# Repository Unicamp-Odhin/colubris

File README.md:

# Estação metereologica LoRaWAN | Colubris

A Colubris é uma placa de hardware aberto baseada no microcontrolador ESP32-S2 e equipada com um módulo LoRa SX1262 integrado. Além disso, ela possui um sistema de gerenciamento de bateria que permite carregar e utilizar baterias diretamente pela placa. A principal finalidade da Colubris é equipar estações meteorológicas que operarão em áreas remotas, mas ela é versátil o suficiente para ser usada em outros dispositivos que necessitem de comunicação de longo alcance.

## Desenvolvedores:

Autor: Julio Nunes Avelar.

## Hardware

Principal:

- ESP32S2/ESP32
- EByte E22-900M22 (SX1262)
- TP4056
- DW01
- 8205A
- Mosfet Canal P IRF4905 ou IRF9540
- Diodo Schottky 1n5819
- PCB impressa
- Botões
- Resistores diversos
- Capacitores diveros

A lista completa pode ser consultada na [documentação](https://embarcacoes.ic.unicamp.br/colubris/build/)

Opcional:

- Modulo de Carga TP4056
- Bateria 18650 4.2V 2600mAh
- DHT22
- Sensor de Umidade do Solo
- Sensor de Nivel de Água
- Sensor de Chuva
- Sensor de Vento
- BME280
- BH1750
- Display OLED 0.96" 128x64 I2C
- Case 3D impressa em ABS

## Software

- [ESP-IDF](https://docs.espressif.com/projects/esp-idf/en/latest/esp32/)

## Pré-requisitos:

- [ESP-IDF](https://docs.espressif.com/projects/esp-idf/en/latest/esp32/get-started/).

Você precisara do ESPIDF para compilar e gravar o Firmware na Placa.

## Configurações:

O Firmware está localizado em colubris, para acessar o diretorio use:

```bash
cd colubris
```

## Menu config:

Para gravar o firmware será necessario realizar alguns ajustes no menu config.

Para "invocar" o ESPID, utilize:

```bash
get_idf
```

Após invocar o IDF, nó diretorio, será necessario escolher o MCU, para utilizar o ESP32S2, utilize:

```bash
idf.py set-target esp32s2
```

Se você estiver usando a extensão do VS-Code, existe uma opção para isso no menu inferior (Elá tem uma caixa com engrenagens como icone e do lado esta escrito esp32 ou esp32s2).

Após escolher o MCU, sera necessario realizar algumas configurações no menu config.

Para acessar o menuconfig utilize:

```bash
idf.py menuconfig
```

ou utilize a opção da extensão do VS-Code (Esta opção também está no menu inferior e tem como icone uma unica engrenagem),

Após acessar menuconfig, configure as seguintes opções:

- Configure a flash com 80mhz.
- Coloque a flash com tamanho minimo de 4 MBs.
- Escolha uma tabela de partições personalizadas.
- Coloque a frequencia da CPU em 240mhz.
- Habilite o https_client.
- Habilite a calibração do ADC.
- Habilite o componente esp_https_server.

Após realizar essas configurações, salve e saia.

## Gravando:

Para realizar a gravação primeiro será necessario realizar a compilação do firmware, é possivel compilar utilizando o comando

```bash
idf.py build
```

Após compilar o firmware para gravalo utilize:

```bash
idf.py flash
```

Caso queira utilizar o monitor serial para ver os logs, utilize:

```bash
idf.py monitor
```

Para executar tudo de uma vez, utilize:

```bash
idf.py build flash monitor
```

Esse passo a passo também pode ser realizado pela extensão do ESPIDF para o VS-Code, basta selecionar a opção: **"ESP-IDF build, flash and monitor"**.

## Organização do Projeto

O projeto é organizado em sete pastas principais:

- **3d-design**: Esta pasta contém os modelos 3D desenvolvidos para o projeto.

- **docs**: Toda a documentação dos componentes e do projeto está localizada nesta pasta.

- **colubris**: Esta pasta armazena o firmware oficial do projeto.

- **documents**: Nesta pasta, você encontrará esquemáticos compilados e datasheets relacionados ao projeto.

- **kicad-project**: Aqui estão o projeto KiCad da placa de circuito impresso (PCB) e os esquemáticos do projeto.

- **examples**: Esta pasta oferece exemplos de uso do projeto para facilitar a implementação.

O projeto foi organizado dessa forma para facilitar o acesso a diferentes aspectos e componentes do projeto.

## Duvidas e Bugs:

Em caso de alguma duvida, bug na aplicação ou sujestão, utilize o menu issues do [Gitlab](https://gitlab.com/embarcacoes/estacao-metereologica-lorawan/-/issues).

## Licença:

O hardware é disponibilizado sob a [CERN Open Hardware Licence (OHL) V2](https://gitlab.com/embarcacoes/estacao-metereologica-lorawan/-/blob/main/LICENSE.md?ref_type=heads), na versão Weakly Reciprocal [(CERN OHL-W)](https://gitlab.com/embarcacoes/estacao-metereologica-lorawan/-/blob/main/LICENSE.md?ref_type=heads). A licença pode ser encontrada na raiz do [repositório](https://gitlab.com/embarcacoes/estacao-metereologica-lorawan/-/blob/main/LICENSE.md?ref_type=heads).

O software é disponibilizado sob a [Licença MIT](https://gitlab.com/embarcacoes/estacao-metereologica-lorawan/-/blob/main/colubris/LICENSE.md?ref_type=heads), que também pode ser consultada no [GitLab](https://gitlab.com/embarcacoes/estacao-metereologica-lorawan/-/blob/main/colubris/LICENSE.md?ref_type=heads).

A documentação é disponibilizada sob a [Licença Creative Commons](https://gitlab.com/embarcacoes/estacao-metereologica-lorawan/-/blob/main/docs/LICENSE.md?ref_type=heads) e também está acessível no [GitLab](https://gitlab.com/embarcacoes/estacao-metereologica-lorawan/-/blob/main/docs/LICENSE.md?ref_type=heads).

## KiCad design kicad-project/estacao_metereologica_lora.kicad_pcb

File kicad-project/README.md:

# Estação metereologica LoRa | Colubris

Os footprints e simbolos externos utilizados estão disponveis na pasta components. Os arquivos gerber para produção estão disponiveis na pasta gerber to order.

Na pasta 3d-design está o STL da placa.

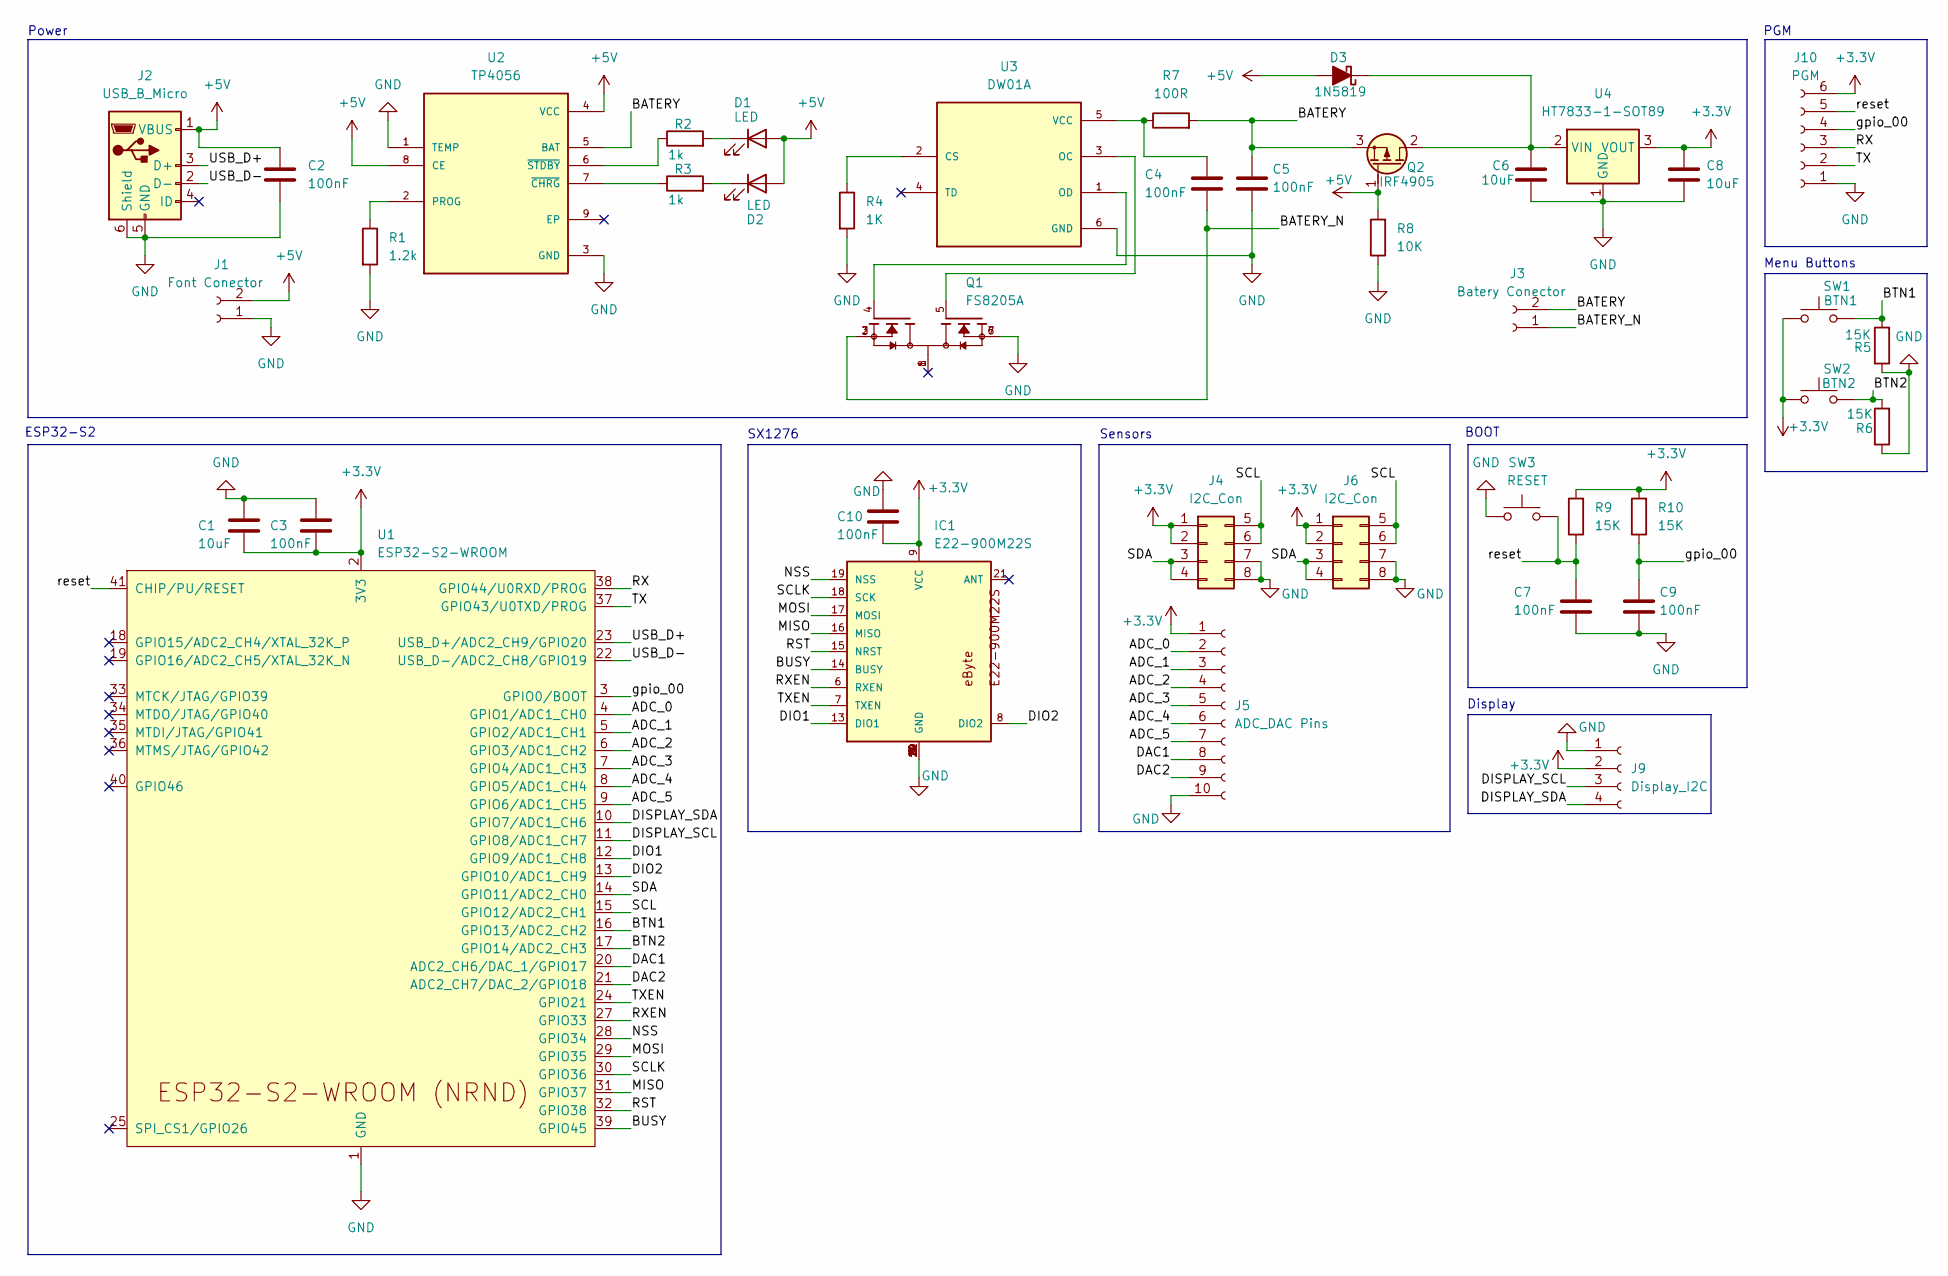
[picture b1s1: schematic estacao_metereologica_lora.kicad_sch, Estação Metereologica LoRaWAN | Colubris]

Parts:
C1, C6, C8: 10uF; C_1206_3216Metric
C2, C3, C4, C5, C7, C9, C10: 100nF; C_1206_3216Metric
D1, D2: LED; LED_1206_3216Metric
D3: 1N5819; D_SOD-123
IC1: E22-900M22S
J1: Font Conector; PinHeader_1x02_P2.54mm_Vertical
J2: USB_B_Micro; USB_Micro-B_GCT_USB3076-30-A
J3: Batery Conector; PinHeader_1x02_P2.54mm_Vertical
J4, J6: I2C_Con; PinHeader_2x04_P2.54mm_Vertical
J5: ADC_DAC Pins; PinSocket_1x10_P2.54mm_Vertical
J9: Display_I2C; PinHeader_1x04_P2.54mm_Vertical
J10: PGM; PinHeader_1x06_P2.54mm_Vertical
Q1: FS8205A; PARTREV 1.7
Q2: IRF4905; TO-220-3_Vertical
R1: 1.2k; R_1206_3216Metric
R2, R3: 1k; R_1206_3216Metric
R4: 1K; R_1206_3216Metric
R5, R6, R9, R10: 15K; R_1206_3216Metric
R7: 100R; R_1206_3216Metric
R8: 10K; R_1206_3216Metric
SW1: BTN1; SW_Tactile_SPST_NO_Straight_CK_PTS636Sx25SMTRLFS
SW2: BTN2; SW_Tactile_SPST_NO_Straight_CK_PTS636Sx25SMTRLFS
SW3: RESET; SW_Tactile_SPST_NO_Straight_CK_PTS636Sx25SMTRLFS
U1: ESP32-S2-WROOM
U2: TP4056; SOP127P600X175-9N
U3: DW01A; PARTREV 1.8
U4: HT7833-1-SOT89; SOT-89-3

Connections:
+3.3V: C1.2, C3.2, C8.1, C10.2, IC1.9 (VCC), J4.1, J4.2, J5.1, J6.1, J6.2, J9.2, J10.6, R9.2, R10.2, SW1.1, SW2.1, U1.2 (3V3), U4.3 (VOUT)
+5V: C2.1, D1.2 (A), D2.2 (A), D3.2 (A), J1.2, J2.1 (VBUS), Q2.1 (G), R8.2, U2.4 (VCC), U2.8 (CE)
/ADC_0: J5.2, U1.4 (GPIO1/ADC1_CH0)
/ADC_1: J5.3, U1.5 (GPIO2/ADC1_CH1)
/ADC_2: J5.4, U1.6 (GPIO3/ADC1_CH2)
/ADC_3: J5.5, U1.7 (GPIO4/ADC1_CH3)
/ADC_4: J5.6, U1.8 (GPIO5/ADC1_CH4)
/ADC_5: J5.7, U1.9 (GPIO6/ADC1_CH5)
/BATERY: C5.1, J3.2, Q2.3 (S), R7.2, U2.5 (BAT)
/BATERY_N: C4.2, J3.1, Q1.2, Q1.3
/BTN1: R5.2, SW1.2, U1.16 (GPIO13/ADC2_CH2)
/BTN2: R6.2, SW2.2, U1.17 (GPIO14/ADC2_CH3)
/BUSY: IC1.14 (BUSY), U1.39 (GPIO45)
/DAC1: J5.8, U1.20 (ADC2_CH6/DAC_1/GPIO17)
/DAC2: J5.9, U1.21 (ADC2_CH7/DAC_2/GPIO18)
/DIO1: IC1.13 (DIO1), U1.12 (GPIO9/ADC1_CH8)
/DIO2: IC1.8 (DIO2), U1.13 (GPIO10/ADC1_CH9)
/DISPLAY_SCL: J9.3, U1.11 (GPIO8/ADC1_CH7)
/DISPLAY_SDA: J9.4, U1.10 (GPIO7/ADC1_CH6)
/MISO: IC1.16 (MISO), U1.31 (GPIO37)
/MOSI: IC1.17 (MOSI), U1.29 (GPIO35)
/NSS: IC1.19 (NSS), U1.28 (GPIO34)
/RST: IC1.15 (NRST), U1.32 (GPIO38)
/RX: J10.3, U1.38 (GPIO44/U0RXD/PROG)
/RXEN: IC1.6 (RXEN), U1.27 (GPIO33)
/SCL: J4.5, J4.6, J6.5, J6.6, U1.15 (GPIO12/ADC2_CH1)
/SCLK: IC1.18 (SCK), U1.30 (GPIO36)
/SDA: J4.3, J4.4, J6.3, J6.4, U1.14 (GPIO11/ADC2_CH0)
/TX: J10.2, U1.37 (GPIO43/U0TXD/PROG)
/TXEN: IC1.7 (TXEN), U1.24 (GPIO21)
/USB_D+: J2.3 (D+), U1.23 (USB_D+/ADC2_CH9/GPIO20)
/USB_D-: J2.2 (D-), U1.22 (USB_D-/ADC2_CH8/GPIO19)
/gpio_00: C9.1, J10.4, R10.1, U1.3 (GPIO0/BOOT)
/reset: C7.1, J10.5, R9.1, SW3.2, U1.41 (CHIP/PU/RESET)
GND: C1.1, C2.2, C3.1, C5.2, C6.2, C7.2, C8.2, C9.2, C10.1, IC1.1 (GND), IC1.2 (GND), IC1.3 (GND), IC1.4 (GND), IC1.5 (GND), IC1.10 (GND), IC1.11 (GND), IC1.12 (GND), IC1.20 (GND), IC1.22 (GND), J1.1, J2.5 (GND), J2.6 (Shield), J4.7, J4.8, J5.10, J6.7, J6.8, J9.1, J10.1, Q1.6, Q1.7, R1.2, R4.2, R5.1, R6.1, R8.1, SW3.1, U1.1 (GND), U1.26 (GND), U1.42 (GND), U1.43 (GND), U2.1 (TEMP), U2.3 (GND), U3.6 (GND), U4.1 (GND)
unnamed: D1.1 (K), R2.2
unnamed: D2.1 (K), R3.2
unnamed: C6.1, D3.1 (K), Q2.2 (D), U4.2 (VIN)
unnamed: R1.1, U2.2 (PROG)
unnamed: R3.1, U2.7 (~CHRG)
unnamed: R2.1, U2.6 (~STDBY)
unnamed: R4.1, U3.2 (CS)
unnamed: Q1.5, U3.3 (OC)
unnamed: Q1.4, U3.1 (OD)
unnamed: C4.1, R7.1, U3.5 (VCC)

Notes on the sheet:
SX1276
Menu Buttons
ESP32-S2
BOOT
PGM
Power
Display
Sensors

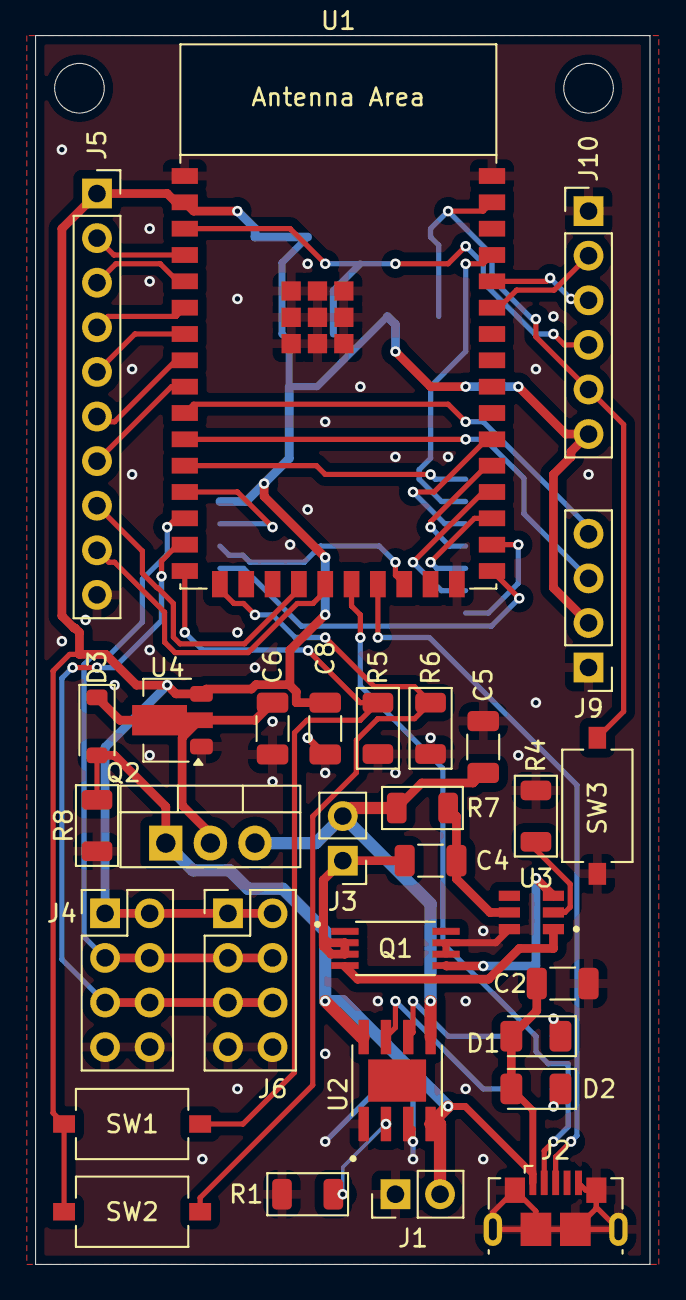
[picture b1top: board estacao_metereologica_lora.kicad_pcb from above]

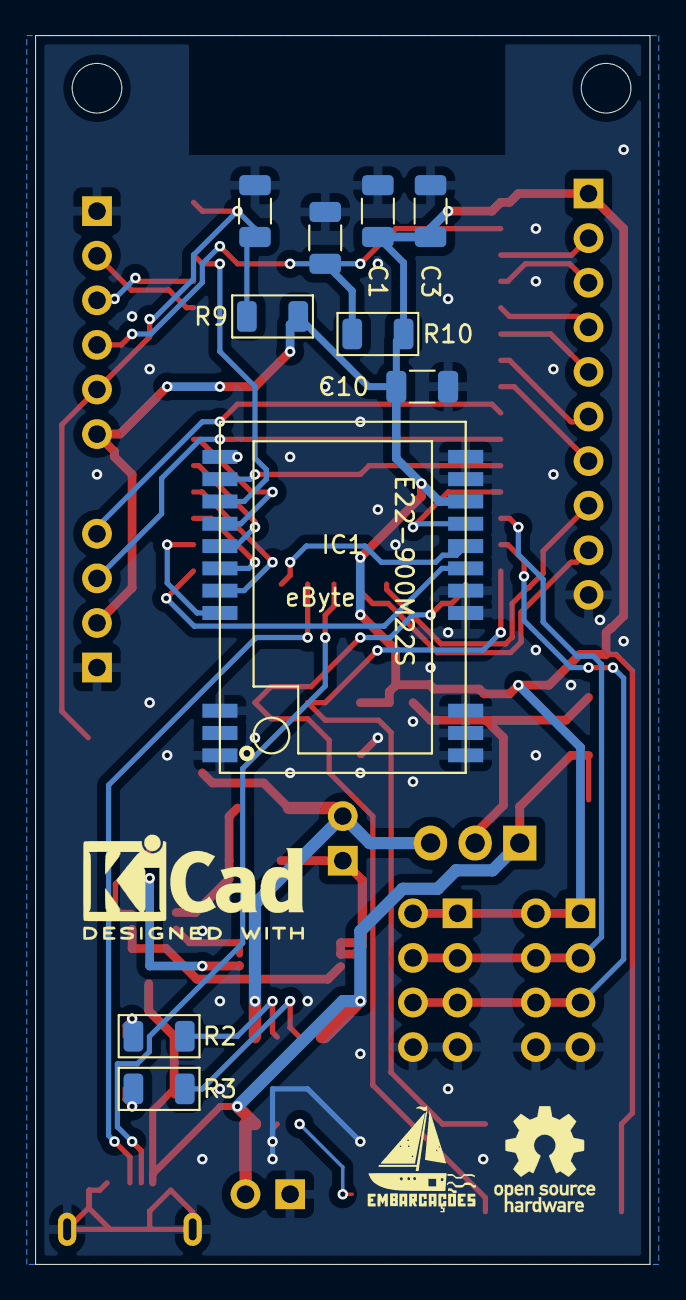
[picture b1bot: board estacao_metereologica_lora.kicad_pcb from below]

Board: 2 copper layers, 35.0 x 70.0 mm, 41 parts (10 on the bottom side), 45 nets.

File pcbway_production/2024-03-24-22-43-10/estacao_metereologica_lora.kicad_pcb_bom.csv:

designator,quantity,value,pack,mpn,mount_type
"C1, C6, C8",3,10uF,C_1206_3216Metric,,smt
"C10, C2, C3, C4, C5, C7, C9",7,100nF,C_1206_3216Metric,,smt
"D1, D2",2,LED,LED_1206_3216Metric,,smt
D3,1,1N5819,D_SOD-123,,smt
IC1,1,E22-900M22S,E22-900M22S,,smt
J1,1,Font Conector,PinHeader_1x02_P2.54mm_Vertical,,tht
J10,1,PGM,PinHeader_1x06_P2.54mm_Vertical,,tht
J2,1,USB_B_Micro,USB_Micro-B_GCT_USB3076-30-A,,smt
J3,1,Batery Conector,PinHeader_1x02_P2.54mm_Vertical,,tht
"J4, J6",2,I2C_Con,PinHeader_2x04_P2.54mm_Vertical,,tht
J5,1,ADC_DAC Pins,PinSocket_1x10_P2.54mm_Vertical,,tht
J9,1,Display_I2C,PinHeader_1x04_P2.54mm_Vertical,,tht
Q1,1,FS8205A,FS8205A,,smt
Q2,1,IRF4905,TO-220-3_Vertical,,tht
R1,1,1.2k,R_1206_3216Metric,,smt
"R10, R5, R6, R9",4,15K,R_1206_3216Metric,,smt
"R2, R3",2,1k,R_1206_3216Metric,,smt
R4,1,1K,R_1206_3216Metric,,smt
R7,1,100R,R_1206_3216Metric,,smt
R8,1,10K,R_1206_3216Metric,,smt
SW1,1,BTN1,SW_Tactile_SPST_NO_Straight_CK_PTS636Sx25SMTRLFS,,smt
SW2,1,BTN2,SW_Tactile_SPST_NO_Straight_CK_PTS636Sx25SMTRLFS,,smt
SW3,1,RESET,SW_Tactile_SPST_NO_Straight_CK_PTS636Sx25SMTRLFS,,smt
U1,1,ESP32-S2-WROOM,ESP32-S2-WROOM,,smt
U2,1,TP4056,SOP127P600X175-9N,,smt
U3,1,DW01A,DW01A,,smt
U4,1,HT7833-1-SOT89,SOT-89-3,,smt

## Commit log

2024-03-25 Configure SAST in `.gitlab-ci.yml`, creating this file if it does not already exist
2024-03-25 Iniciando projeto com esquematicos
2024-03-25 Atualizando esquematico
2024-03-25 Removendo gitlab-ci
2024-04-29 Adicionando esquematico e componentes usados
    Adicionando PDF do esquematico, footprints, simbolos e outras coisas
    utilizadas no projeto
2024-04-29 Reestruturando o projeto
    Colocando o design da PCB em local especifico e criando novas pastas
2024-04-29 Continuando reestruturação
2024-04-29 Adicionando licença e contributing
2024-04-29 Criando novas pastas
    Criando pasta com modelos 3d, documentação, e software
2024-04-29 Add .gitlab-ci.yml
2024-04-29 Adicionando imagens e começando a escrever documentação
2024-04-29 atualizando footer da documentação
2024-04-29 criand script de deploy
2024-04-29 atualizando script de deploy
2024-04-30 Adicionando licensas de software e documentação
2024-04-30 atualizando licença de software
2024-04-30 Atualizando documentação
2024-04-30 Atualizando home da documentação
2024-04-30 Add CHANGELOG
2024-04-30 Atualizando README
2024-04-30 corrigindo pequeno erro no readme
2024-04-30 Adicionando datasheets e referencias tecnicas
    Adicionando datasheets e referencias do ESP32S2 e do SX1262
2024-06-07 alterando arquivo de configuração do MKDOCS
2024-06-07 alterando copyright da licença
